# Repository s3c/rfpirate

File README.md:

rfpirate
========

General purpose ISM interfacing hardware based on the CC1101

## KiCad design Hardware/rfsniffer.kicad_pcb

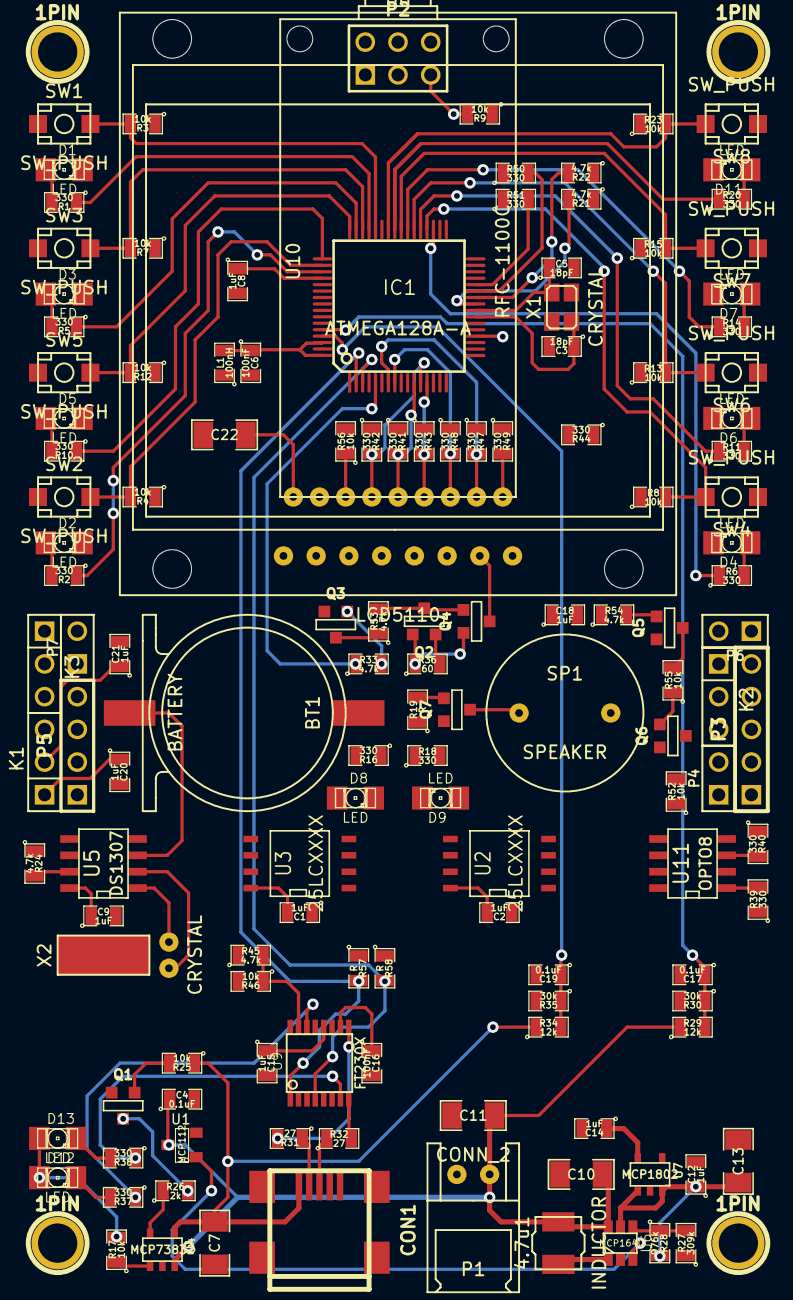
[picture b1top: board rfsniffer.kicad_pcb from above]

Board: 4 copper layers, 140 parts (0 on the bottom side), 101 nets.

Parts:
1PIN, 1PIN#2, 1PIN#3, 1PIN#4: P***; 1pin
4.7u1: INDUCTOR; LQH44P
BT1: BATTERY; CR1220H
C1, C2, C8, C9, C12, C14, C15, C18, C20, C21: 1uF; SM0805
C3, C5: 18pF; SM0805
C4, C17, C19: 0.1uF; SM0805
C6, C16: 100nF; SM0805
C7, C10, C11: 4.7uF; SM1206
C13: 10uF; SM1206
C22: C; SM1206
CON1: USB-MINI-B; USB_MINI_B
D1, D2, D3, D4, D5, D6, D7, D8, D9, D11, D12, D13: LED; LED-1206
IC1: ATMEGA128A-A; TQFP_64
K1, K2, K3: CONN_3; PIN_ARRAY_3X1
L1: 100nH; SM0805
P1: CONN_2; S2B-XH-A
P2: AVR_ISP; pin_array_3x2
P3: CONN_5; PIN_ARRAY_5x1
P4, P6, P7: CONN_2; PIN_ARRAY_2X1
P5: CONN_4; PIN_ARRAY_4x1
Q1, Q3, Q5, Q7: BC817; SOT23EBC
Q2, Q4, Q6: BC807; SOT23EBC
R1, R2, R5, R6, R10, R11, R14, R16, R18, R20, R37, R38, R39, R40, R41, R42, R43, R44, R47, R48, R49, R50, R51: 330; SM0805
R3, R4, R7, R8, R9, R12, R13, R15, R17, R23, R25, R46, R52, R55, R56: 10k; SM0805
R19, R57, R58: R; SM0805
R21, R22, R24, R33, R45, R53, R54: 4.7k; SM0805
R26: 2k; SM0805
R27: 309k; SM0805
R28: 976k; SM0805
R29, R34: 12k; SM0805
R30, R35: 30k; SM0805
R31, R32: 27; SM0805
R36: 60; SM0805
SP1: SPEAKER; BUZZER_12MM
SW1, SW2, SW3, SW4, SW5, SW6, SW7, SW8: SW_PUSH; TD-85XU
U1: MCP112; SOT23
U2, U3: 25LCXXXX; SO8N
U4: MCP73832; SOT23-5
U5: DS1307; SO8E
U6: MCP1640; SOT23_6
U7: MCP1802; SOT23-5
U8: LCD5110
U9: FT230X; SSOP17
U10: RFC-1100C
U11: OPTO8; SO8E
X1: CRYSTAL; TSX-3225
X2: CRYSTAL; LFXTAL002997

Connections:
3.3V: C1.2, C2.2, C8.1, C14.1, C18.1, C21.1, D12.1, D13.1, IC1.21, IC1.52, K1.2, L1.1, P2.2, R3.1, R4.1, R7.1, R8.1, R9.1, R12.1, R13.1, R15.1, R17.2, R21.1, R22.1, R23.1, R24.1, R52.2, U2.8, U3.8, U7.5, U8.6, U9.3, U9.11
5V: C9.1, C12.1, C13.1, C15.1, C20.1, C22.1, K1.1, Q2.1, Q6.1, R28.2, R36.2, SP1.1, U5.8, U6.5, U7.1, U7.3, U9.12, U10.1
AVCC: C6.1, IC1.62, IC1.64, L1.2
BATSENSE: C17.1, IC1.60, R29.2, R30.1
BTN1: IC1.44, R3.2, SW1.2
BTN2: IC1.46, R7.2, SW3.2
BTN3: IC1.48, R12.2, SW5.2
BTN4: IC1.50, R4.2, SW2.2
BTN5: IC1.36, R8.2, SW4.2
BTN6: IC1.38, R13.2, SW6.2
BTN7: IC1.40, R15.2, SW7.2
BTN8: IC1.42, R23.2, SW8.2
CCONT: Q1.2, R25.2
CSRF: R49.2, U10.9
CSTATUS: R17.1, U4.1
D+: CON1.3, R32.1
D-: CON1.2, R31.1
GDO0: IC1.7, R47.2, U10.8
GDO2: IC1.8, R48.2, U10.7
GND: BT1.2, C1.1, C2.1, C3.2, C4.2, C5.2, C6.2, C7.2, C8.2, C9.2, C10.2, C11.2, C12.2, C13.2, C14.2, C15.2, C16.2, C17.2, C18.2, C19.2, C20.2, C21.2, C22.2, CON1.5, CON1.6, CON1.7, CON1.8, CON1.9, D1.2, D2.2, D3.2, D4.2, D5.2, D6.2, D7.2, D8.2, D9.2, D11.2, IC1.22, IC1.53, IC1.63, K1.3, K2.3, K3.3, P1.2, P2.6, P3.5, P5.4, Q1.1, Q3.1, Q5.1, Q7.1, R27.1, R30.2, R35.2, R46.2, R56.2, SW1.1, SW2.1, SW3.1, SW4.1, SW5.1, SW6.1, SW7.1, SW8.1, U1.2, U2.4, U3.4, U4.2, U5.4, U6.2, U7.2, U8.8, U9.5, U9.13, U10.2, U11.2, U11.5
LCDBL: IC1.5, R33.1
LCDBLPWR: Q4.3, U8.7
LED1: IC1.45, R1.1
LED2: IC1.47, R5.1
LED3: IC1.49, R10.1
LED4: IC1.51, R2.1
LED5: IC1.35, R6.1
LED6: IC1.37, R11.1
LED7: IC1.39, R14.1
LED8: IC1.41, R20.1
unnamed: P5.2, R48.1
unnamed: P5.1, R47.1
unnamed: D7.1, R14.2
unnamed: R40.2, U11.3
unnamed: R39.2, U11.1
unnamed: K3.2, R51.1
unnamed: K3.1, R50.1
unnamed: P3.4, R44.1
unnamed: P3.3, R43.1
unnamed: P3.2, R42.1
unnamed: P3.1, R41.1
unnamed: R27.2, R28.1, U6.4
unnamed: C16.1, U9.10
unnamed: 4.7u1.2, U6.1
unnamed: Q3.2, R33.2
unnamed: Q3.3, R53.1
unnamed: Q2.3, Q4.2, R53.2
unnamed: Q2.2, Q4.1, R36.1
unnamed: Q5.2, R54.2
unnamed: Q6.2, R55.1
unnamed: R31.2, U9.9
unnamed: R32.2, U9.8
unnamed: P7.2, R58.1
unnamed: P7.1, R57.1
unnamed: Q5.3, R55.2
unnamed: Q7.2, R19.2
unnamed: Q7.3, SP1.2
unnamed: P5.3, R49.1
unnamed: D11.1, R20.2
unnamed: U5.2, X2.1
unnamed: U5.1, X2.2
unnamed: D5.1, R10.2
unnamed: D2.1, R2.2
unnamed: D3.1, R5.2
unnamed: D9.1, R18.2
unnamed: Q1.3, R26.2
unnamed: R26.1, U4.5
unnamed: R37.1, U9.14
unnamed: R38.1, U9.7
unnamed: D13.2, R38.2
unnamed: D12.2, R37.2
unnamed: D6.1, R11.2
unnamed: D4.1, R6.2
unnamed: D1.1, R1.2
unnamed: D8.1, R16.2
OPTOIN: R52.1, U11.6
OPTOINC+: P6.1, R40.1
OPTOINC-: P6.2, U11.4
OPTOOUTC+: P4.1, U11.8
OPTOOUTC-: P4.2, U11.7
OUTRTC: IC1.6, R24.2, U5.7
PAMP: Q6.3, R56.1, U10.3
RESET: IC1.20, P2.5, R9.2
RTS: IC1.9, U9.2
SCK: IC1.11, P2.3, R41.2, U2.6, U3.6, U8.5, U10.5
SCL: IC1.25, K2.2, R21.2, U5.6
SDA: IC1.26, K2.1, R22.2, U5.5
SI: IC1.12, R42.2, U2.5, U3.5, U8.4, U10.4
SO: IC1.13, R43.2, U2.2, U3.2, U10.6
UARTRX: IC1.2, P2.4, R57.2, U9.1
UARTRX2: IC1.27, R50.2
UARTTX: IC1.3, P2.1, R58.2, U9.4
UARTTX2: IC1.28, R51.2
USBSENSE: C19.1, IC1.61, R34.2, R35.1
VBAT: 4.7u1.1, C4.1, C10.1, C11.1, P1.1, R29.1, U1.3, U4.3, U6.6
VBATLOW: U1.1, U6.3
VBATRTC: BT1.1, U5.3
VUSB: C7.1, CON1.1, R25.1, R34.1, R45.1, U4.4
VUSBS: R45.2, R46.1, U9.15
XTAL1: C5.1, IC1.24, X1.2
XTAL2: C3.1, IC1.23, X1.1

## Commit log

2014-06-17 Initial thoughts on how this will be implemented.
2014-08-13 Laptop move
2014-08-17 Added initial hardware design
2014-08-17 Cleanup
2014-09-02 Works works works...
2014-09-10 Small hardware changes
2014-10-23 Initial hardware layout
2014-10-28 Another hardware attempt, TQFP64 footprint mismatch
